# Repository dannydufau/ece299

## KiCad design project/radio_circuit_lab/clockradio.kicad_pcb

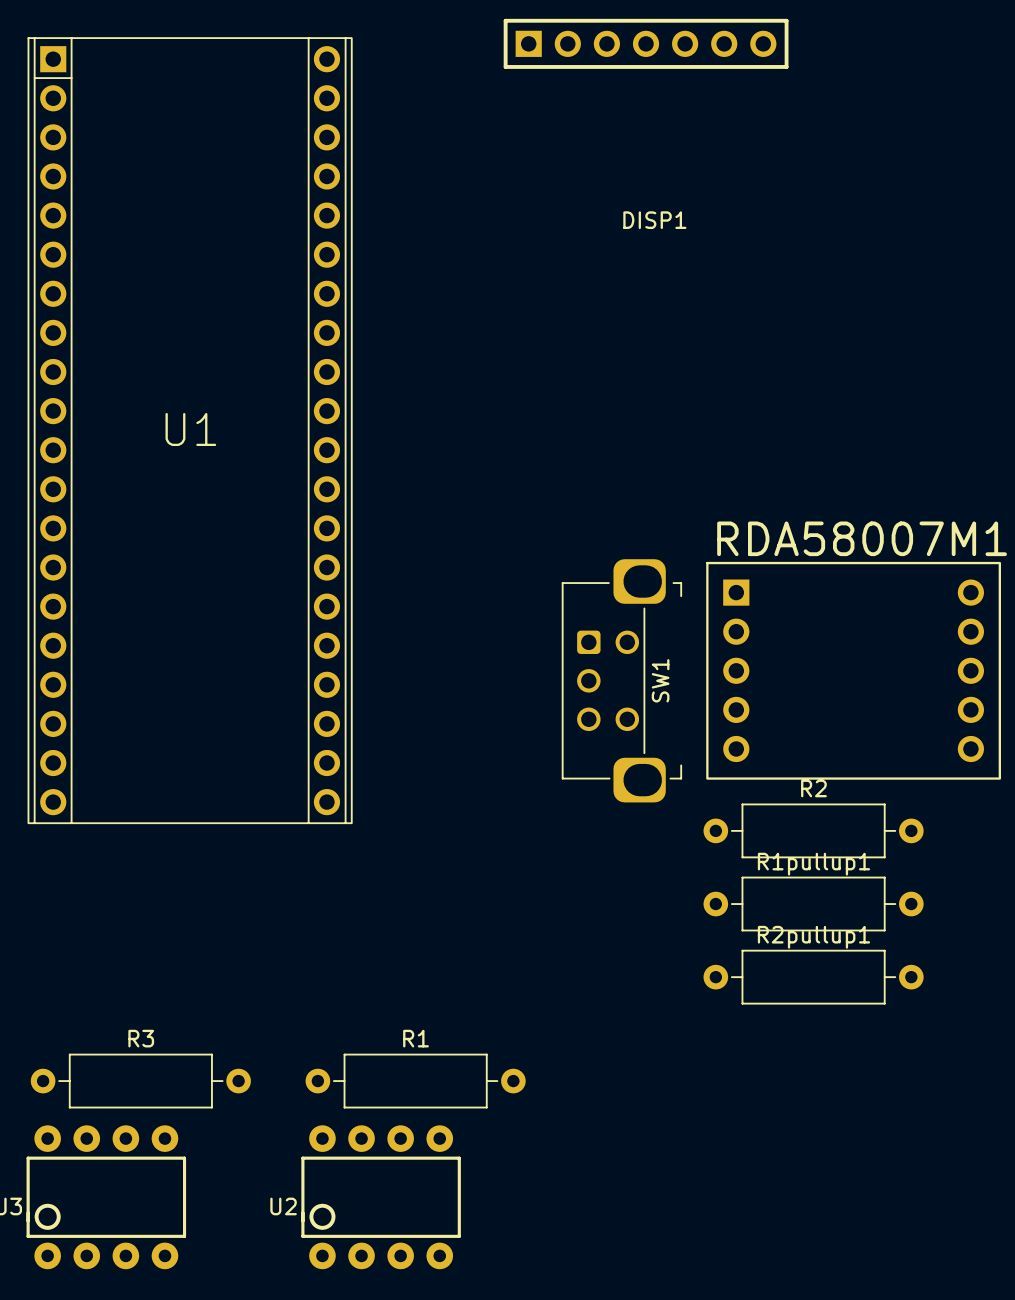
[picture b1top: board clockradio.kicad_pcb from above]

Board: 2 copper layers, 11 parts (0 on the bottom side), 13 nets, no tracks yet.

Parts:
DISP1: OLED Display; OLED_Display_1.3
R1, R3: R 10Ω; R_Axial_DIN0309_L9.0mm_D3.2mm_P12.70mm_Horizontal
R1pullup1, R2pullup1: 2k; R_Axial_DIN0309_L9.0mm_D3.2mm_P12.70mm_Horizontal
R2: R; R_Axial_DIN0309_L9.0mm_D3.2mm_P12.70mm_Horizontal
RDA58007M1: RDA5807M_Module_TH
SW1: RotaryEncoder_Switch; RotaryEncoder_Bourns_Horizontal_PEC12R-2x17F-Sxxxx
U1: RPi_Pico_TH
U2, U3: LM386; DIP08

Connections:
+3.3V: DISP1.2 (VDD), R1pullup1.1, R2pullup1.1, RDA58007M1.5 (VDD), SW1.C, U1.36 (3V3)
+5V: U1.40 (VBUS), U2.6 (V+), U3.6 (V+)
GND: DISP1.1 (VSS/GND), R1.2, R2.2, R3.2, RDA58007M1.6 (GND), SW1.S2, U1.38 (GND), U2.2 (-), U2.4 (GND), U3.2 (-), U3.4 (GND)
GPIO2: DISP1.3 (SCLK), U1.4 (GP2)
GPIO3: DISP1.4 (SDA), U1.5 (GP3)
GPIO4: DISP1.5 (RES), U1.6 (GP4)
GPIO5: DISP1.6 (DC), U1.7 (GP5)
GPIO6: DISP1.7 (CS), U1.9 (GP6)
GPIO18: SW1.A, U1.24 (GP18)
GPIO19: SW1.B, U1.25 (GP19)
GPIO20: SW1.S1, U1.26 (GP20)
GPIO26: RDA58007M1.1 (SDIO), U1.31 (GP26/ADC0)
GPIO27: R1pullup1.2, R2pullup1.2, RDA58007M1.2 (SCLK), U1.32 (GP27/ADC1)

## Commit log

2024-06-13 Add lab1 report
2024-06-13 Added lab2
2024-06-13 Lab2: Add blink.py
2024-06-13 lab2: add naive button
2024-06-13 lab2: update runner to update display on button event
2024-06-14 Add lab2 kicad files and schematic
2024-06-17 Add kicad project
2024-06-17 updates to project schematic
2024-06-21 Save experiments. Save actual project code under code
2024-06-21 runner cleanup
2024-06-21 Add lab3
2024-06-26 Project updates
2024-06-26 Update project
2024-06-27 Working menu with encoder and aux button
2024-07-03 kicad updates
2024-07-08 Dynamic menu loading
2024-07-08 Dynamic menu loading - save files from pico to here
2024-07-11 Add alarm sound schematic
2024-07-11 Add global label for GPIO22 on alarm circuit
2024-07-11 Remaining files for alarm circuit update
2024-07-11 Support for setting time
2024-07-11 24h and 12h time supported
2024-07-12 Support saving and displaying alarm
2024-07-14 Working alarm
2024-07-15 Add led.py, move out max_recursion
2024-07-15 Add ms on function for led.py. Return none when no alarm set
2024-07-15 Add default alarm time if none set prior to write
2024-07-16 Multiple alarms
2024-07-16 Remove alarms with duplicate times
2024-07-24 Working time functions
2024-07-30 final
2024-08-02 Run Black
2024-08-05 Complete project
